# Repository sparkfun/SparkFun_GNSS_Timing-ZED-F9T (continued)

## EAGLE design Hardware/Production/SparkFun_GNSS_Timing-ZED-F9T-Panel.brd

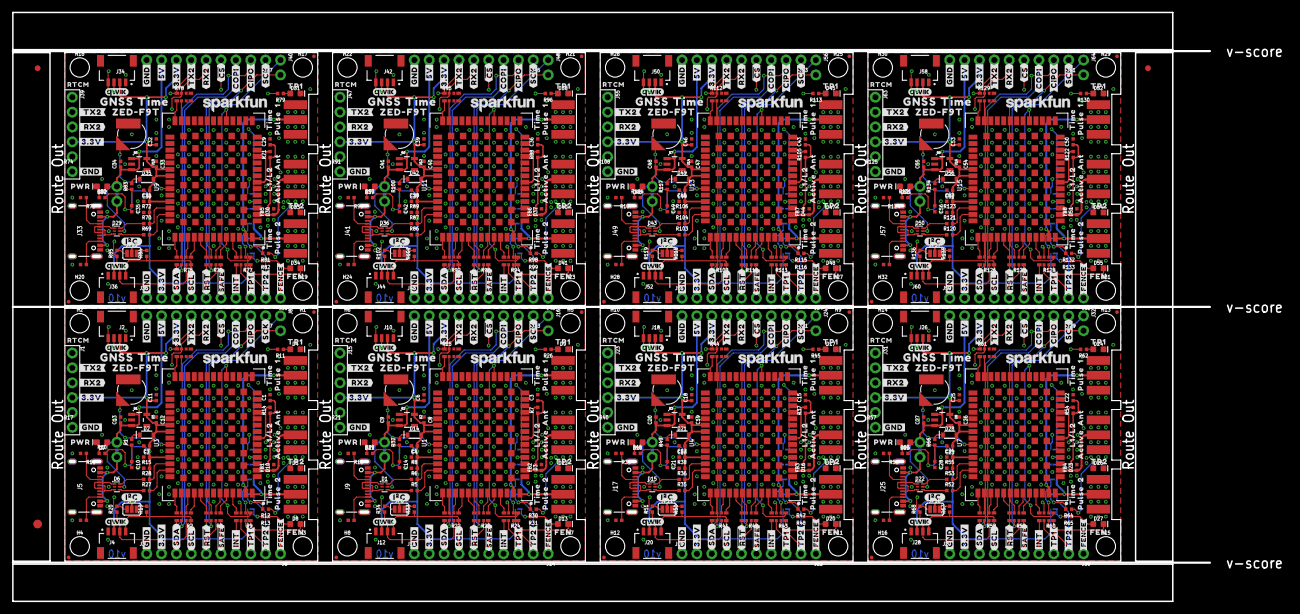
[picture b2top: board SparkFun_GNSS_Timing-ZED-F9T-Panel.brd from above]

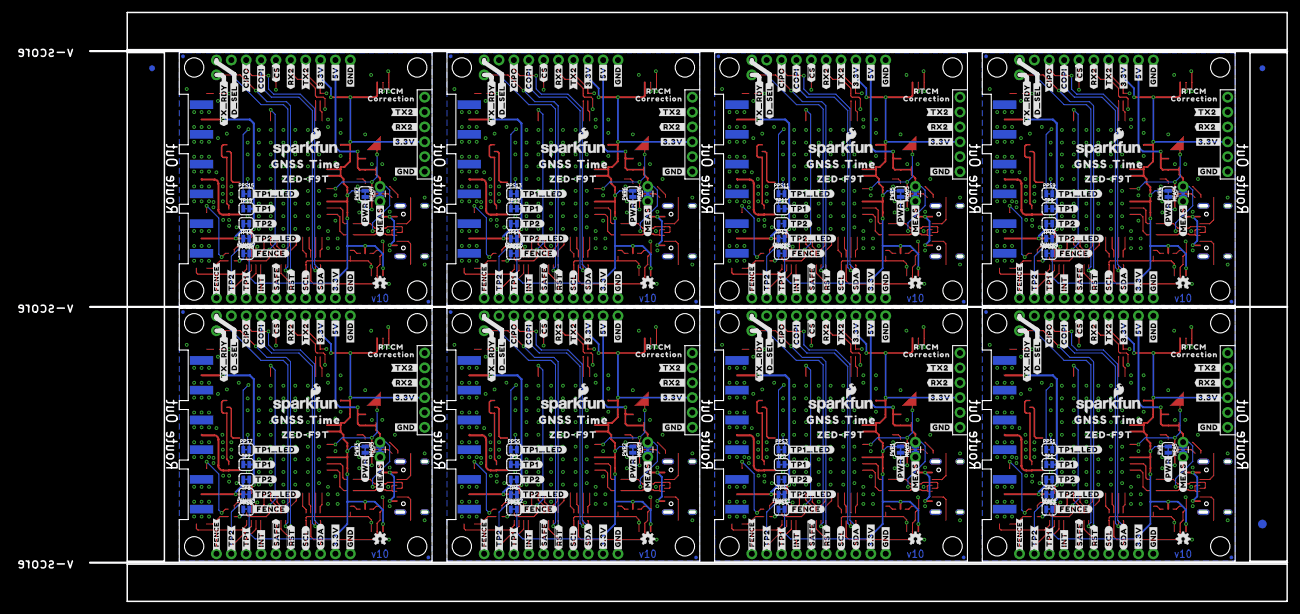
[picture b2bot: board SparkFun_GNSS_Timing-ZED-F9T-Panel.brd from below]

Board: 4 copper layers, 204.5 x 100.6 mm, 1158 parts (379 on the bottom side), 456 nets.

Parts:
B1, B2, B3, B4, B5, B6, B7, B8: 6.8MM_COIN_CELL; ML414H_IV01E
C1, C3, C15, C22, C29, C36, C43, C50: 47pF; 0402-TIGHT
C2, C4, C6, C9, C10, C11, C13, C14, C16, C18, C20, C21, C23, C25, C27, C28, C30, C32, C34, C35, C37, C39, C41, C42, C44, C46, C48, C49, C51, C53, C55, C56: 1.0uF; 0402-TIGHT
C5, C7, C8, C12, C17, C19, C24, C26, C31, C33, C38, C40, C45, C47, C52, C54: 0.1uF; 0402-TIGHT
D1, D6, D15, D22, D29, D36, D43, D50: PRTR5V0U2F; SOT886
D2, D14, D21, D28, D35, D42, D49, D56: 0.5A/40V/420mV; SOD-323
D3, D10, D16, D23, D30, D37, D44, D51: PESD0402-0402T; 0402-TIGHT
D4, D9, D17, D24, D31, D38, D45, D52: YEL; LED-0603
D5, D12, D19, D26, D33, D40, D47, D54: GRN; LED-0603
D7, D11, D18, D25, D32, D39, D46, D53: RED; LED-0603
D8, D13, D20, D27, D34, D41, D48, D55: BLU; LED-0603
E1, E2, E3, E4, E5, E6, E7, E8, E9, E10, E11, E12, E13, E14, E15, E16, E17, E18, E19, E20, E21, E22, E23, E24: SMA; SMA-EDGE
E$1, E$2, E$3, E$4: FIDUCIAL-1X2
E$5, E$6: FIDUCIAL-1.5X3
FB1, FB2, FB3, FB4, FB5, FB6, FB7, FB8: 2.66Ω; 0402-TIGHT
FENCE, FENCE1, FENCE2, FENCE3, FENCE4, FENCE5, FENCE6, FENCE7: JUMPER-SMT_2_NC_TRACE_SILK; SMT-JUMPER_2_NC_TRACE_SILK
H1, H2, H3, H4, H5, H6, H7, H8, H9, H10, H11, H12, H13, H14, H15, H16, H17, H18, H19, H20, H21, H22, H23, H24, H25, H26, H27, H28, H29, H30, H31, H32: STAND-OFF
J1, J15, J23, J31, J39, J47, J55, J63: Radio; 1X06_NO_SILK
J2, J4, J10, J12, J18, J20, J26, J28, J34, J36, J42, J44, J50, J52, J58, J60: Qwiic Right Angle; JST04_1MM_RA
J3, J11, J19, J27, J35, J43, J51, J59: PTH; 1X04_NO_SILK
J5, J9, J17, J25, J33, J41, J49, J57: USB Female Type C Connector; USB-C-16P_4LAYER-PADS
J6, J14, J22, J30, J38, J46, J54, J62: 1X06_NO_SILK
J7, J13, J21, J29, J37, J45, J53, J61: 1X09_NO_SILK
J8, J16, J24, J32, J40, J48, J56, J64: 1X02_NO_SILK
JP1, JP2, JP3, JP4, JP7, JP8, JP9, JP10, JP12, JP13, JP14, JP15, JP17, JP18, JP19, JP20, JP21, JP23, JP24, JP25, JP26, JP28, JP29, JP30, JP31, JP33, JP34, JP35, JP36, JP61, JP71, JP81: FIDUCIALUFIDUCIAL; FIDUCIAL-MICRO
JP5, JP6, JP11, JP16, JP22, JP27, JP32, JP37: JUMPER-SMT_3_NO_SILK; SMT-JUMPER_3_NO_SILK
LOGO1, LOGO6, LOGO11, LOGO16, LOGO21, LOGO26, LOGO31, LOGO36: OSHW-LOGOMINI; OSHW-LOGO-MINI
LOGO2, LOGO7, LOGO12, LOGO17, LOGO22, LOGO27, LOGO32, LOGO37: SFE_LOGO_NAME_FLAME.1_INCH; SFE_LOGO_NAME_FLAME_.1
LOGO3, LOGO4, LOGO8, LOGO10, LOGO13, LOGO15, LOGO18, LOGO20, LOGO23, LOGO25, LOGO28, LOGO30, LOGO33, LOGO35, LOGO38, LOGO40: QWIIC_LOGO_4MM; QWIIC_4MM
LOGO5, LOGO9, LOGO14, LOGO19, LOGO24, LOGO29, LOGO34, LOGO39: SFE_LOGO_NAME.1_INCH; SFE_LOGO_NAME_.1
MEAS, MEAS1, MEAS2, MEAS3, MEAS4, MEAS5, MEAS6, MEAS7: JUMPER-COMBO_2_NC_TRACE; COMBO-JUMPER_2_NC_TRACE
PPS1, PPS2, PPS3, PPS4, PPS5, PPS6, PPS7, PPS8, PPS9, PPS10, PPS11, PPS12, PPS13, PPS14, PPS15, PPS16: JUMPER-SMT_2_NC_TRACE_SILK; SMT-JUMPER_2_NC_TRACE_SILK
PWR, PWR1, PWR2, PWR3, PWR4, PWR5, PWR6, PWR7: JUMPER-SMT_2_NC_TRACE_SILK; SMT-JUMPER_2_NC_TRACE_SILK
R1, R32, R49, R66, R83, R100, R117, R134: 3.3K; 0402-TIGHT
R2, R3, R4, R9, R22, R23, R24, R25, R41, R42, R43, R44, R58, R59, R60, R61, R75, R76, R77, R78, R92, R93, R94, R95, R109, R110, R111, R112, R126, R127, R128, R129: 33; 1206_RA
R5, R6, R27, R28, R35, R36, R52, R53, R69, R70, R86, R87, R103, R104, R120, R121: 27OHM; 0402-TIGHT
R7, R14, R37, R54, R71, R88, R105, R122: 10Ω; 0402-TIGHT
R8, R15, R38, R55, R72, R89, R106, R123: 100k; 0402-TIGHT
R10, R11, R12, R13, R26, R29, R30, R31, R45, R46, R47, R48, R62, R63, R64, R65, R79, R80, R81, R82, R96, R97, R98, R99, R113, R114, R115, R116, R130, R131, R132, R133: 1k; 0402-TIGHT
R16, R17, R18, R21, R39, R40, R56, R57, R73, R74, R90, R91, R107, R108, R124, R125: 5.1k; 0402-TIGHT
R19, R20, R33, R34, R50, R51, R67, R68, R84, R85, R101, R102, R118, R119, R135, R136: 2.2k; 0402-TIGHT
TP1, TP2, TP3, TP4, TP5, TP6, TP7, TP8, TP9, TP10, TP11, TP12, TP13, TP14, TP15, TP16: JUMPER-SMT_2_NC_TRACE_SILK; SMT-JUMPER_2_NC_TRACE_SILK
U1, U3, U4, U7, U9, U11, U13, U15: U-BLOX_ZED_F9T; ZED-F9X
U2, U5, U6, U8, U10, U12, U14, U16: AP2112K-3.3V; SOT23-5
U$1, U$29, U$35, U$36, U$59, U$60, U$88, U$106, U$108, U$109, U$127, U$128, U$165, U$183, U$185, U$186, U$204, U$205, U$242, U$260, U$262, U$263, U$281, U$282, U$319, U$337, U$339, U$340, U$358, U$359, U$396, U$414, U$416, U$417, U$435, U$436, U$473, U$491, U$493, U$494, U$512, U$513, U$550, U$568, U$570, U$571, U$589, U$590: #3#3V#0
U$2, U$6, U$155, U$232, U$309, U$386, U$463, U$540: L1#L20
U$3, U$28, U$89, U$105, U$166, U$182, U$243, U$259, U$320, U$336, U$397, U$413, U$474, U$490, U$551, U$567: #5V#1
U$4, U$27, U$38, U$39, U$61, U$62, U$90, U$104, U$110, U$111, U$129, U$130, U$167, U$181, U$187, U$188, U$206, U$207, U$244, U$258, U$264, U$265, U$283, U$284, U$321, U$335, U$341, U$342, U$360, U$361, U$398, U$412, U$418, U$419, U$437, U$438, U$475, U$489, U$495, U$496, U$514, U$515, U$552, U$566, U$572, U$573, U$591, U$592: #GND#2
U$5, U$8, U$91, U$92, U$168, U$169, U$245, U$246, U$322, U$323, U$399, U$400, U$476, U$477, U$553, U$554: ##CS##4
U$7, U$21, U$80, U$83, U$157, U$160, U$234, U$237, U$311, U$314, U$388, U$391, U$465, U$468, U$542, U$545: TIME0
U$9, U$10, U$93, U$94, U$170, U$171, U$247, U$248, U$324, U$325, U$401, U$402, U$478, U$479, U$555, U$556: #CIPO#6
U$11, U$12, U$95, U$96, U$172, U$173, U$249, U$250, U$326, U$327, U$403, U$404, U$480, U$481, U$557, U$558: #COPI#5
U$13, U$79, U$156, U$233, U$310, U$387, U$464, U$541: ACTIVE1
U$14, U$16, U$97, U$98, U$174, U$175, U$251, U$252, U$328, U$329, U$405, U$406, U$482, U$483, U$559, U$560: #RX2#1
U$15, U$37, U$112, U$113, U$189, U$190, U$266, U$267, U$343, U$344, U$420, U$421, U$497, U$498, U$574, U$575: ##RST##0
U$17, U$53, U$87, U$99, U$164, U$176, U$241, U$253, U$318, U$330, U$395, U$407, U$472, U$484, U$549, U$561: #SCL#3
U$18, U$22, U$100, U$101, U$177, U$178, U$254, U$255, U$331, U$332, U$408, U$409, U$485, U$486, U$562, U$563: #SDA#2
U$19, U$25, U$81, U$84, U$158, U$161, U$235, U$238, U$312, U$315, U$389, U$392, U$466, U$469, U$543, U$546: PULSE1
U$20, U$82, U$159, U$236, U$313, U$390, U$467, U$544: 12
U$23, U$24, U$102, U$103, U$179, U$180, U$256, U$257, U$333, U$334, U$410, U$411, U$487, U$488, U$564, U$565: #TX2#0
U$26, U$85, U$162, U$239, U$316, U$393, U$470, U$547: 20
U$30, U$107, U$184, U$261, U$338, U$415, U$492, U$569: #SCK#5
U$31, U$86, U$163, U$240, U$317, U$394, U$471, U$548: ANT1
U$32, U$136, U$213, U$290, U$367, U$444, U$521, U$598: #_TX2#0
U$33, U$135, U$212, U$289, U$366, U$443, U$520, U$597: #D_SEL#1
U$34, U$77, U$146, U$153, U$223, U$230, U$300, U$307, U$377, U$384, U$454, U$461, U$531, U$538, U$608, U$615: ZED#F9T0
U$40, U$70, U$144, U$151, U$221, U$228, U$298, U$305, U$375, U$382, U$452, U$459, U$529, U$536, U$606, U$613: GNSS0
U$41, U$114, U$191, U$268, U$345, U$422, U$499, U$576: ##SAFE##1
U$42, U$43, U$115, U$116, U$192, U$193, U$269, U$270, U$346, U$347, U$423, U$424, U$500, U$501, U$577, U$578: #INT#2
U$44, U$65, U$121, U$133, U$198, U$210, U$275, U$287, U$352, U$364, U$429, U$441, U$506, U$518, U$583, U$595: #FENCE#0
U$45, U$126, U$203, U$280, U$357, U$434, U$511, U$588: #TP2_LED#0
U$46, U$47, U$117, U$118, U$194, U$195, U$271, U$272, U$348, U$349, U$425, U$426, U$502, U$503, U$579, U$580: #TP1#3
U$48, U$49, U$119, U$120, U$196, U$197, U$273, U$274, U$350, U$351, U$427, U$428, U$504, U$505, U$581, U$582: #TP2#4
U$50, U$123, U$200, U$277, U$354, U$431, U$508, U$585: #TP2#0
U$51, U$122, U$199, U$276, U$353, U$430, U$507, U$584: #_FENCE#0
U$52, U$124, U$201, U$278, U$355, U$432, U$509, U$586: #TP1#0
U$54, U$125, U$202, U$279, U$356, U$433, U$510, U$587: #TP1_LED#0
U$55, U$139, U$216, U$293, U$370, U$447, U$524, U$601: #_RX2#0
U$56, U$137, U$214, U$291, U$368, U$445, U$522, U$599: PWR0
U$57, U$138, U$215, U$292, U$369, U$446, U$523, U$600: #PWR#0
U$58, U$140, U$217, U$294, U$371, U$448, U$525, U$602: #RX2_#0
U$63, U$131, U$208, U$285, U$362, U$439, U$516, U$593: TP10
U$64, U$132, U$209, U$286, U$363, U$440, U$517, U$594: TP21
U$66, U$141, U$218, U$295, U$372, U$449, U$526, U$603: #TX2_#0
U$67, U$134, U$211, U$288, U$365, U$442, U$519, U$596: #TX_RDY#0
U$68, U$142, U$219, U$296, U$373, U$450, U$527, U$604: #MEAS#0
U$69, U$143, U$220, U$297, U$374, U$451, U$528, U$605: #I�C#0
U$71, U$74, U$145, U$152, U$222, U$229, U$299, U$306, U$376, U$383, U$453, U$460, U$530, U$537, U$607, U$614: TIME1
U$72, U$147, U$224, U$301, U$378, U$455, U$532, U$609: ##SAFE##0
U$73, U$148, U$225, U$302, U$379, U$456, U$533, U$610: RTCM0
U$75, U$149, U$226, U$303, U$380, U$457, U$534, U$611: CORRECTION1
U$76, U$150, U$227, U$304, U$381, U$458, U$535, U$612: RTCM_0
U$78, U$154, U$231, U$308, U$385, U$462, U$539, U$616: FEN0

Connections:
3.3V: C2.1, C7.2, C11.1, C12.2, D2.A, FENCE.2, J1.4, J2.2, J3.2, J4.2, J7.7, JP5.2, PWR.2, R15.2, U3.33, U3.34, U3.38, U5.5
3.3V1: C4.1, C5.2, C6.1, C8.2, D14.A, FENCE1.2, J10.2, J11.2, J12.2, J13.7, J15.4, JP6.2, PWR1.2, R8.2, U1.33, U1.34, U1.38, U2.5
3.3V2: C16.1, C17.2, C18.1, C19.2, D21.A, FENCE2.2, J18.2, J19.2, J20.2, J21.7, J23.4, JP11.2, PWR2.2, R38.2, U4.33, U4.34, U4.38, U6.5
3.3V3: C23.1, C24.2, C25.1, C26.2, D28.A, FENCE3.2, J26.2, J27.2, J28.2, J29.7, J31.4, JP16.2, PWR3.2, R55.2, U7.33, U7.34, U7.38, U8.5
3.3V4: C30.1, C31.2, C32.1, C33.2, D35.A, FENCE4.2, J34.2, J35.2, J36.2, J37.7, J39.4, JP22.2, PWR4.2, R72.2, U9.33, U9.34, U9.38, U10.5
3.3V5: C37.1, C38.2, C39.1, C40.2, D42.A, FENCE5.2, J42.2, J43.2, J44.2, J45.7, J47.4, JP27.2, PWR5.2, R89.2, U11.33, U11.34, U11.38, U12.5
3.3V6: C44.1, C45.2, C46.1, C47.2, D49.A, FENCE6.2, J50.2, J51.2, J52.2, J53.7, J55.4, JP32.2, PWR6.2, R106.2, U13.33, U13.34, U13.38, U14.5
3.3V7: C51.1, C52.2, C53.1, C54.2, D56.A, FENCE7.2, J58.2, J59.2, J60.2, J61.7, J63.4, JP37.2, PWR7.2, R123.2, U15.33, U15.34, U15.38, U16.5
5V: C13.1, D6.5, J7.8, MEAS.2, MEAS.4, U5.1, U5.3
5V1: C9.1, D1.5, J13.8, MEAS1.2, MEAS1.4, U2.1, U2.3
5V2: C20.1, D15.5, J21.8, MEAS2.2, MEAS2.4, U6.1, U6.3
5V3: C27.1, D22.5, J29.8, MEAS3.2, MEAS3.4, U8.1, U8.3
5V4: C34.1, D29.5, J37.8, MEAS4.2, MEAS4.4, U10.1, U10.3
5V5: C41.1, D36.5, J45.8, MEAS5.2, MEAS5.4, U12.1, U12.3
5V6: C48.1, D43.5, J53.8, MEAS6.2, MEAS6.4, U14.1, U14.3
5V7: C55.1, D50.5, J61.8, MEAS7.2, MEAS7.4, U16.1, U16.3
!RESET!: J6.6, R3.P7
!RESET!1: J14.6, R23.P7
!RESET!2: J22.6, R42.P7
!RESET!3: J30.6, R59.P7
!RESET!4: J38.6, R76.P7
!RESET!5: J46.6, R93.P7
!RESET!6: J54.6, R110.P7
!RESET!7: J62.6, R127.P7
!RESET!_LV: R3.P2, U3.49
!RESET!_LV1: R23.P2, U1.49
!RESET!_LV2: R42.P2, U4.49
!RESET!_LV3: R59.P2, U7.49
!RESET!_LV4: R76.P2, U9.49
!RESET!_LV5: R93.P2, U11.49
!RESET!_LV6: R110.P2, U13.49
!RESET!_LV7: R127.P2, U15.49
!SAFE!: J6.5, R3.P8
!SAFE!1: J14.5, R23.P8
!SAFE!2: J22.5, R42.P8
!SAFE!3: J30.5, R59.P8
!SAFE!4: J38.5, R76.P8
!SAFE!5: J46.5, R93.P8
!SAFE!6: J54.5, R110.P8
!SAFE!7: J62.5, R127.P8
!SAFE!_LV: R3.P1, U3.50
!SAFE!_LV1: R23.P1, U1.50
!SAFE!_LV2: R42.P1, U4.50
!SAFE!_LV3: R59.P1, U7.50
!SAFE!_LV4: R76.P1, U9.50
!SAFE!_LV5: R93.P1, U11.50
!SAFE!_LV6: R110.P1, U13.50
!SAFE!_LV7: R127.P1, U15.50
ANT_VCC: C1.1, FB1.2, R14.1
ANT_VCC1: C3.1, FB2.2, R7.1
ANT_VCC2: C15.1, FB3.2, R37.1
ANT_VCC3: C22.1, FB4.2, R54.1
ANT_VCC4: C29.1, FB5.2, R71.1
ANT_VCC5: C36.1, FB6.2, R88.1
ANT_VCC6: C43.1, FB7.2, R105.1
ANT_VCC7: C50.1, FB8.2, R122.1
CC1: J5.A5, R17.2
CC2: J5.B5, R16.2
CC3: J9.A5, R21.2
CC4: J9.B5, R18.2
CC5: J17.A5, R40.2
CC6: J17.B5, R39.2
CC7: J25.A5, R57.2
CC8: J25.B5, R56.2
CC9: J33.A5, R74.2
CC10: J33.B5, R73.2
CC11: J41.A5, R91.2
CC12: J41.B5, R90.2
CC13: J49.A5, R108.2
CC14: J49.B5, R107.2
CC15: J57.A5, R125.2
CC16: J57.B5, R124.2
D+: D6.4, R27.1
D+1: D1.4, R5.1
D+2: D15.4, R35.1
D+3: D22.4, R52.1
D+4: D29.4, R69.1
D+5: D36.4, R86.1
D+6: D43.4, R103.1
D+7: D50.4, R120.1
D-: D6.6, R28.1
D-1: D1.6, R6.1
D-2: D15.6, R36.1
D-3: D22.6, R53.1
D-4: D29.6, R70.1
D-5: D36.6, R87.1
D-6: D43.6, R104.1
D-7: D50.6, R121.1
DSEL_LV: R3.P3, U3.47
DSEL_LV1: R23.P3, U1.47
DSEL_LV2: R42.P3, U4.47
DSEL_LV3: R59.P3, U7.47
DSEL_LV4: R76.P3, U9.47
DSEL_LV5: R93.P3, U11.47
DSEL_LV6: R110.P3, U13.47
DSEL_LV7: R127.P3, U15.47
D_SEL: J8.1, R3.P6
D_SEL1: J16.1, R23.P6
D_SEL2: J24.1, R42.P6
D_SEL3: J32.1, R59.P6
D_SEL4: J40.1, R76.P6
D_SEL5: J48.1, R93.P6
D_SEL6: J56.1, R110.P6
D_SEL7: J64.1, R127.P6
EXTINT: J6.4, R9.P5
EXTINT1: J14.4, R24.P5
EXTINT2: J22.4, R43.P5
EXTINT3: J30.4, R60.P5
EXTINT4: J38.4, R77.P5
EXTINT5: J46.4, R94.P5
EXTINT6: J54.4, R111.P5
EXTINT7: J62.4, R128.P5
EXTINT_LV: R9.P4, U3.51
EXTINT_LV1: R24.P4, U1.51
EXTINT_LV2: R43.P4, U4.51
EXTINT_LV3: R60.P4, U7.51
EXTINT_LV4: R77.P4, U9.51
EXTINT_LV5: R94.P4, U11.51
EXTINT_LV6: R111.P4, U13.51
EXTINT_LV7: R128.P4, U15.51
FENCE_LV: R9.P1, U3.19
FENCE_LV1: R24.P1, U1.19
FENCE_LV2: R43.P1, U4.19
FENCE_LV3: R60.P1, U7.19
FENCE_LV4: R77.P1, U9.19
FENCE_LV5: R94.P1, U11.19
FENCE_LV6: R111.P1, U13.19
FENCE_LV7: R128.P1, U15.19
FENCE_STAT: D8.C, J6.1, R9.P8
FENCE_STAT1: D13.C, J14.1, R24.P8
FENCE_STAT2: D20.C, J22.1, R43.P8
FENCE_STAT3: D27.C, J30.1, R60.P8
FENCE_STAT4: D34.C, J38.1, R77.P8
FENCE_STAT5: D41.C, J46.1, R94.P8
FENCE_STAT6: D48.C, J54.1, R111.P8
FENCE_STAT7: D55.C, J62.1, R128.P8
GND: B1.-, C1.2, C2.2, C7.1, C10.2, C11.2, C12.1, C13.2, D4.C, D5.C, D6.2, D7.C, D10.2, E1.GND@0, E1.GND@1, E1.GND@2, E1.GND@3, E2.GND@0, E2.GND@1, E2.GND@2, E2.GND@3, E3.GND@0, E3.GND@1, E3.GND@2, E3.GND@3, J1.6, J2.1, J3.1, J4.1, J5.GND, J5.GND2, J7.9, R15.1, R16.1, R17.1, U3.1, U3.3, U3.12, U3.14, U3.32, U3.37, U3.41, U3.48, U3.G1, U3.G2, U3.G3, U3.G4, U3.G5, U3.G6, U3.G7, U3.G8, U3.G9, U3.G10, U3.G11, U3.G12, U3.G13, U3.G14, U3.G15, U3.G16, U3.G17, U3.G18, U3.G19, U3.G20, U3.G21, U3.G22, U3.G23, U3.G24, U3.G25, U3.G26, U3.G27, U3.G28, U3.G29, U3.G30, U3.G31, U3.G32, U3.G33, U3.G34, U3.G35, U3.G36, U3.G37, U3.G38, U3.G39, U3.G40, U3.G41, U3.G42, U3.G43, U3.G44, U3.G45, U3.G46, U3.G47, U3.G48, U5.2
GND1: B2.-, C3.2, C4.2, C5.1, C6.2, C8.1, C9.2, C14.2, D1.2, D3.2, D9.C, D11.C, D12.C, E4.GND@0, E4.GND@1, E4.GND@2, E4.GND@3, E5.GND@0, E5.GND@1, E5.GND@2, E5.GND@3, E6.GND@0, E6.GND@1, E6.GND@2, E6.GND@3, J9.GND, J9.GND2, J10.1, J11.1, J12.1, J13.9, J15.6, R8.1, R18.1, R21.1, U1.1, U1.3, U1.12, U1.14, U1.32, U1.37, U1.41, U1.48, U1.G1, U1.G2, U1.G3, U1.G4, U1.G5, U1.G6, U1.G7, U1.G8, U1.G9, U1.G10, U1.G11, U1.G12, U1.G13, U1.G14, U1.G15, U1.G16, U1.G17, U1.G18, U1.G19, U1.G20, U1.G21, U1.G22, U1.G23, U1.G24, U1.G25, U1.G26, U1.G27, U1.G28, U1.G29, U1.G30, U1.G31, U1.G32, U1.G33, U1.G34, U1.G35, U1.G36, U1.G37, U1.G38, U1.G39, U1.G40, U1.G41, U1.G42, U1.G43, U1.G44, U1.G45, U1.G46, U1.G47, U1.G48, U2.2
GND2: B3.-, C15.2, C16.2, C17.1, C18.2, C19.1, C20.2, C21.2, D15.2, D16.2, D17.C, D18.C, D19.C, E7.GND@0, E7.GND@1, E7.GND@2, E7.GND@3, E8.GND@0, E8.GND@1, E8.GND@2, E8.GND@3, E9.GND@0, E9.GND@1, E9.GND@2, E9.GND@3, J17.GND, J17.GND2, J18.1, J19.1, J20.1, J21.9, J23.6, R38.1, R39.1, R40.1, U4.1, U4.3, U4.12, U4.14, U4.32, U4.37, U4.41, U4.48, U4.G1, U4.G2, U4.G3, U4.G4, U4.G5, U4.G6, U4.G7, U4.G8, U4.G9, U4.G10, U4.G11, U4.G12, U4.G13, U4.G14, U4.G15, U4.G16, U4.G17, U4.G18, U4.G19, U4.G20, U4.G21, U4.G22, U4.G23, U4.G24, U4.G25, U4.G26, U4.G27, U4.G28, U4.G29, U4.G30, U4.G31, U4.G32, U4.G33, U4.G34, U4.G35, U4.G36, U4.G37, U4.G38, U4.G39, U4.G40, U4.G41, U4.G42, U4.G43, U4.G44, U4.G45, U4.G46, U4.G47, U4.G48, U6.2
GND3: B4.-, C22.2, C23.2, C24.1, C25.2, C26.1, C27.2, C28.2, D22.2, D23.2, D24.C, D25.C, D26.C, E10.GND@0, E10.GND@1, E10.GND@2, E10.GND@3, E11.GND@0, E11.GND@1, E11.GND@2, E11.GND@3, E12.GND@0, E12.GND@1, E12.GND@2, E12.GND@3, J25.GND, J25.GND2, J26.1, J27.1, J28.1, J29.9, J31.6, R55.1, R56.1, R57.1, U7.1, U7.3, U7.12, U7.14, U7.32, U7.37, U7.41, U7.48, U7.G1, U7.G2, U7.G3, U7.G4, U7.G5, U7.G6, U7.G7, U7.G8, U7.G9, U7.G10, U7.G11, U7.G12, U7.G13, U7.G14, U7.G15, U7.G16, U7.G17, U7.G18, U7.G19, U7.G20, U7.G21, U7.G22, U7.G23, U7.G24, U7.G25, U7.G26, U7.G27, U7.G28, U7.G29, U7.G30, U7.G31, U7.G32, U7.G33, U7.G34, U7.G35, U7.G36, U7.G37, U7.G38, U7.G39, U7.G40, U7.G41, U7.G42, U7.G43, U7.G44, U7.G45, U7.G46, U7.G47, U7.G48, U8.2
GND4: B5.-, C29.2, C30.2, C31.1, C32.2, C33.1, C34.2, C35.2, D29.2, D30.2, D31.C, D32.C, D33.C, E13.GND@0, E13.GND@1, E13.GND@2, E13.GND@3, E14.GND@0, E14.GND@1, E14.GND@2, E14.GND@3, E15.GND@0, E15.GND@1, E15.GND@2, E15.GND@3, J33.GND, J33.GND2, J34.1, J35.1, J36.1, J37.9, J39.6, R72.1, R73.1, R74.1, U9.1, U9.3, U9.12, U9.14, U9.32, U9.37, U9.41, U9.48, U9.G1, U9.G2, U9.G3, U9.G4, U9.G5, U9.G6, U9.G7, U9.G8, U9.G9, U9.G10, U9.G11, U9.G12, U9.G13, U9.G14, U9.G15, U9.G16, U9.G17, U9.G18, U9.G19, U9.G20, U9.G21, U9.G22, U9.G23, U9.G24, U9.G25, U9.G26, U9.G27, U9.G28, U9.G29, U9.G30, U9.G31, U9.G32, U9.G33, U9.G34, U9.G35, U9.G36, U9.G37, U9.G38, U9.G39, U9.G40, U9.G41, U9.G42, U9.G43, U9.G44, U9.G45, U9.G46, U9.G47, U9.G48, U10.2
GND5: B6.-, C36.2, C37.2, C38.1, C39.2, C40.1, C41.2, C42.2, D36.2, D37.2, D38.C, D39.C, D40.C, E16.GND@0, E16.GND@1, E16.GND@2, E16.GND@3, E17.GND@0, E17.GND@1, E17.GND@2, E17.GND@3, E18.GND@0, E18.GND@1, E18.GND@2, E18.GND@3, J41.GND, J41.GND2, J42.1, J43.1, J44.1, J45.9, J47.6, R89.1, R90.1, R91.1, U11.1, U11.3, U11.12, U11.14, U11.32, U11.37, U11.41, U11.48, U11.G1, U11.G2, U11.G3, U11.G4, U11.G5, U11.G6, U11.G7, U11.G8, U11.G9, U11.G10, U11.G11, U11.G12, U11.G13, U11.G14, U11.G15, U11.G16, U11.G17, U11.G18, U11.G19, U11.G20, U11.G21, U11.G22, U11.G23, U11.G24, U11.G25, U11.G26, U11.G27, U11.G28, U11.G29, U11.G30, U11.G31, U11.G32, U11.G33, U11.G34, U11.G35, U11.G36, U11.G37, U11.G38, U11.G39, U11.G40, U11.G41, U11.G42, U11.G43, U11.G44, U11.G45, U11.G46, U11.G47, U11.G48, U12.2
GND6: B7.-, C43.2, C44.2, C45.1, C46.2, C47.1, C48.2, C49.2, D43.2, D44.2, D45.C, D46.C, D47.C, E19.GND@0, E19.GND@1, E19.GND@2, E19.GND@3, E20.GND@0, E20.GND@1, E20.GND@2, E20.GND@3, E21.GND@0, E21.GND@1, E21.GND@2, E21.GND@3, J49.GND, J49.GND2, J50.1, J51.1, J52.1, J53.9, J55.6, R106.1, R107.1, R108.1, U13.1, U13.3, U13.12, U13.14, U13.32, U13.37, U13.41, U13.48, U13.G1, U13.G2, U13.G3, U13.G4, U13.G5, U13.G6, U13.G7, U13.G8, U13.G9, U13.G10, U13.G11, U13.G12, U13.G13, U13.G14, U13.G15, U13.G16, U13.G17, U13.G18, U13.G19, U13.G20, U13.G21, U13.G22, U13.G23, U13.G24, U13.G25, U13.G26, U13.G27, U13.G28, U13.G29, U13.G30, U13.G31, U13.G32, U13.G33, U13.G34, U13.G35, U13.G36, U13.G37, U13.G38, U13.G39, U13.G40, U13.G41, U13.G42, U13.G43, U13.G44, U13.G45, U13.G46, U13.G47, U13.G48, U14.2
GND7: B8.-, C50.2, C51.2, C52.1, C53.2, C54.1, C55.2, C56.2, D50.2, D51.2, D52.C, D53.C, D54.C, E22.GND@0, E22.GND@1, E22.GND@2, E22.GND@3, E23.GND@0, E23.GND@1, E23.GND@2, E23.GND@3, E24.GND@0, E24.GND@1, E24.GND@2, E24.GND@3, J57.GND, J57.GND2, J58.1, J59.1, J60.1, J61.9, J63.6, R123.1, R124.1, R125.1, U15.1, U15.3, U15.12, U15.14, U15.32, U15.37, U15.41, U15.48, U15.G1, U15.G2, U15.G3, U15.G4, U15.G5, U15.G6, U15.G7, U15.G8, U15.G9, U15.G10, U15.G11, U15.G12, U15.G13, U15.G14, U15.G15, U15.G16, U15.G17, U15.G18, U15.G19, U15.G20, U15.G21, U15.G22, U15.G23, U15.G24, U15.G25, U15.G26, U15.G27, U15.G28, U15.G29, U15.G30, U15.G31, U15.G32, U15.G33, U15.G34, U15.G35, U15.G36, U15.G37, U15.G38, U15.G39, U15.G40, U15.G41, U15.G42, U15.G43, U15.G44, U15.G45, U15.G46, U15.G47, U15.G48, U16.2
GPS_ANT1: D10.1, E1.SIG, FB1.1, U3.2
GPS_ANT2: D3.1, E4.SIG, FB2.1, U1.2
GPS_ANT3: D16.1, E7.SIG, FB3.1, U4.2
GPS_ANT4: D23.1, E10.SIG, FB4.1, U7.2
GPS_ANT5: D30.1, E13.SIG, FB5.1, U9.2
GPS_ANT6: D37.1, E16.SIG, FB6.1, U11.2
GPS_ANT7: D44.1, E19.SIG, FB7.1, U13.2
GPS_ANT8: D51.1, E22.SIG, FB8.1, U15.2
unnamed: R5.2, U1.40
unnamed: D4.A, R11.1
unnamed: PPS1.1, R11.2
unnamed: J5.VBUS1, J5.VBUS2, MEAS.1, MEAS.3
unnamed: R9.P3, TP1.1
unnamed: D2.C, R1.2
unnamed: R9.P2, TP2.1
unnamed: R6.2, U1.39
unnamed: R7.2, U1.7
unnamed: J9.VBUS1, J9.VBUS2, MEAS1.1, MEAS1.3
unnamed: R27.2, U3.40
unnamed: R28.2, U3.39
unnamed: R14.2, U3.7
unnamed: D7.A, R10.1
unnamed: D9.A, R26.1
unnamed: D5.A, R12.1
unnamed: PPS2.1, R12.2
unnamed: D8.A, R13.1
unnamed: FENCE.1, R13.2
unnamed: PWR.1, R10.2
unnamed: JP5.1, R20.2
unnamed: JP5.3, R19.2
unnamed: PPS3.1, R26.2
unnamed: D11.A, R29.1
unnamed: D12.A, R30.1
unnamed: PPS4.1, R30.2
unnamed: D13.A, R31.1
unnamed: FENCE1.1, R31.2
unnamed: PWR1.1, R29.2
unnamed: D14.C, R32.2
unnamed: JP6.1, R34.2
unnamed: JP6.3, R33.2
unnamed: R24.P3, TP3.1
unnamed: R24.P2, TP4.1
unnamed: R35.2, U4.40
unnamed: R36.2, U4.39
unnamed: R37.2, U4.7
unnamed: J17.VBUS1, J17.VBUS2, MEAS2.1, MEAS2.3
unnamed: D17.A, R45.1
unnamed: PPS5.1, R45.2
unnamed: D18.A, R46.1
unnamed: D19.A, R47.1
unnamed: PPS6.1, R47.2
unnamed: D20.A, R48.1
unnamed: FENCE2.1, R48.2
unnamed: PWR2.1, R46.2
unnamed: D21.C, R49.2
unnamed: JP11.1, R51.2
unnamed: JP11.3, R50.2
unnamed: R43.P3, TP5.1
unnamed: R43.P2, TP6.1
unnamed: R52.2, U7.40
unnamed: R53.2, U7.39
unnamed: R54.2, U7.7
unnamed: J25.VBUS1, J25.VBUS2, MEAS3.1, MEAS3.3
unnamed: D24.A, R62.1
unnamed: PPS7.1, R62.2
unnamed: D25.A, R63.1
unnamed: D26.A, R64.1
unnamed: PPS8.1, R64.2
unnamed: D27.A, R65.1
unnamed: FENCE3.1, R65.2
unnamed: PWR3.1, R63.2
unnamed: D28.C, R66.2
unnamed: JP16.1, R68.2
unnamed: JP16.3, R67.2
unnamed: R60.P3, TP7.1
unnamed: R60.P2, TP8.1
unnamed: R69.2, U9.40
unnamed: R70.2, U9.39
unnamed: R71.2, U9.7
unnamed: J33.VBUS1, J33.VBUS2, MEAS4.1, MEAS4.3
unnamed: D31.A, R79.1
unnamed: PPS9.1, R79.2
unnamed: D32.A, R80.1
unnamed: D33.A, R81.1
unnamed: PPS10.1, R81.2
unnamed: D34.A, R82.1
unnamed: FENCE4.1, R82.2
unnamed: PWR4.1, R80.2
unnamed: D35.C, R83.2
unnamed: JP22.1, R85.2
unnamed: JP22.3, R84.2
unnamed: R77.P3, TP9.1
unnamed: R77.P2, TP10.1
unnamed: R86.2, U11.40
unnamed: R87.2, U11.39
unnamed: R88.2, U11.7
unnamed: J41.VBUS1, J41.VBUS2, MEAS5.1, MEAS5.3
unnamed: D38.A, R96.1
unnamed: PPS11.1, R96.2
unnamed: D39.A, R97.1
unnamed: D40.A, R98.1
unnamed: PPS12.1, R98.2
unnamed: D41.A, R99.1
unnamed: FENCE5.1, R99.2
unnamed: PWR5.1, R97.2
unnamed: D42.C, R100.2
unnamed: JP27.1, R102.2
unnamed: JP27.3, R101.2
unnamed: R94.P3, TP11.1
unnamed: R94.P2, TP12.1
unnamed: R103.2, U13.40
unnamed: R104.2, U13.39
unnamed: R105.2, U13.7
unnamed: J49.VBUS1, J49.VBUS2, MEAS6.1, MEAS6.3
unnamed: D45.A, R113.1
unnamed: PPS13.1, R113.2
unnamed: D46.A, R114.1
unnamed: D47.A, R115.1
unnamed: PPS14.1, R115.2
unnamed: D48.A, R116.1
unnamed: FENCE6.1, R116.2
unnamed: PWR6.1, R114.2
unnamed: D49.C, R117.2
unnamed: JP32.1, R119.2
unnamed: JP32.3, R118.2
unnamed: R111.P3, TP13.1
unnamed: R111.P2, TP14.1
unnamed: R120.2, U15.40
unnamed: R121.2, U15.39
unnamed: R122.2, U15.7
unnamed: J57.VBUS1, J57.VBUS2, MEAS7.1, MEAS7.3
unnamed: D52.A, R130.1
unnamed: PPS15.1, R130.2
unnamed: D53.A, R131.1
unnamed: D54.A, R132.1
unnamed: PPS16.1, R132.2
unnamed: D55.A, R133.1
unnamed: FENCE7.1, R133.2
unnamed: PWR7.1, R131.2
unnamed: D56.C, R134.2
unnamed: JP37.1, R136.2
unnamed: JP37.3, R135.2
unnamed: R128.P3, TP15.1
unnamed: R128.P2, TP16.1
PPS1_STAT: J6.3, PPS1.2, R9.P6
PPS1_STAT1: J14.3, PPS3.2, R24.P6
PPS1_STAT2: J22.3, PPS5.2, R43.P6
PPS1_STAT3: J30.3, PPS7.2, R60.P6
PPS1_STAT4: J38.3, PPS9.2, R77.P6
PPS1_STAT5: J46.3, PPS11.2, R94.P6
PPS1_STAT6: J54.3, PPS13.2, R111.P6
PPS1_STAT7: J62.3, PPS15.2, R128.P6
PPS2_STAT: J6.2, PPS2.2, R9.P7
PPS2_STAT1: J14.2, PPS4.2, R24.P7
PPS2_STAT2: J22.2, PPS6.2, R43.P7
PPS2_STAT3: J30.2, PPS8.2, R60.P7
PPS2_STAT4: J38.2, PPS10.2, R77.P7
PPS2_STAT5: J46.2, PPS12.2, R94.P7
PPS2_STAT6: J54.2, PPS14.2, R111.P7
PPS2_STAT7: J62.2, PPS16.2, R128.P7
RX1_LV: R2.P3, U3.43
RX1_LV1: R22.P3, U1.43
RX1_LV2: R41.P3, U4.43
RX1_LV3: R58.P3, U7.43
RX1_LV4: R75.P3, U9.43
RX1_LV5: R92.P3, U11.43
RX1_LV6: R109.P3, U13.43
RX1_LV7: R126.P3, U15.43
RX2_LV: R4.P2, U3.26
RX2_LV1: R25.P2, U1.26
RX2_LV2: R44.P2, U4.26
RX2_LV3: R61.P2, U7.26
RX2_LV4: R78.P2, U9.26
RX2_LV5: R95.P2, U11.26
RX2_LV6: R112.P2, U13.26
RX2_LV7: R129.P2, U15.26
RXI1: J13.5, J15.3, R25.P7
RXI2: J1.3, J7.5, R4.P7
RXI3: J21.5, J23.3, R44.P7
RXI4: J29.5, J31.3, R61.P7
RXI5: J37.5, J39.3, R78.P7
RXI6: J45.5, J47.3, R95.P7
RXI7: J53.5, J55.3, R112.P7
RXI8: J61.5, J63.3, R129.P7
RXI/COPI: J7.3, R2.P6
RXI/COPI1: J13.3, R22.P6
RXI/COPI2: J21.3, R41.P6
RXI/COPI3: J29.3, R58.P6
RXI/COPI4: J37.3, R75.P6
RXI/COPI5: J45.3, R92.P6
RXI/COPI6: J53.3, R109.P6
RXI/COPI7: J61.3, R126.P6
SCL/SCK: J2.4, J3.4, J4.4, J7.1, R2.P8, R19.1
SCL/SCK1: J10.4, J11.4, J12.4, J13.1, R22.P8, R33.1
SCL/SCK2: J18.4, J19.4, J20.4, J21.1, R41.P8, R50.1
SCL/SCK3: J26.4, J27.4, J28.4, J29.1, R58.P8, R67.1
SCL/SCK4: J34.4, J35.4, J36.4, J37.1, R75.P8, R84.1
SCL/SCK5: J42.4, J43.4, J44.4, J45.1, R92.P8, R101.1
SCL/SCK6: J50.4, J51.4, J52.4, J53.1, R109.P8, R118.1
SCL/SCK7: J58.4, J59.4, J60.4, J61.1, R126.P8, R135.1
SCL_LV: R2.P1, U3.45
SCL_LV1: R22.P1, U1.45
SCL_LV2: R41.P1, U4.45
SCL_LV3: R58.P1, U7.45
SCL_LV4: R75.P1, U9.45
SCL_LV5: R92.P1, U11.45
SCL_LV6: R109.P1, U13.45
SCL_LV7: R126.P1, U15.45
SDA/!CS: J2.3, J3.3, J4.3, J7.4, R2.P7, R20.1
SDA/!CS1: J10.3, J11.3, J12.3, J13.4, R22.P7, R34.1
SDA/!CS2: J18.3, J19.3, J20.3, J21.4, R41.P7, R51.1
SDA/!CS3: J26.3, J27.3, J28.3, J29.4, R58.P7, R68.1
SDA/!CS4: J34.3, J35.3, J36.3, J37.4, R75.P7, R85.1
SDA/!CS5: J42.3, J43.3, J44.3, J45.4, R92.P7, R102.1
SDA/!CS6: J50.3, J51.3, J52.3, J53.4, R109.P7, R119.1
SDA/!CS7: J58.3, J59.3, J60.3, J61.4, R126.P7, R136.1
SDA_LV: R2.P2, U3.44
SDA_LV1: R22.P2, U1.44
SDA_LV2: R41.P2, U4.44
SDA_LV3: R58.P2, U7.44
SDA_LV4: R75.P2, U9.44
SDA_LV5: R92.P2, U11.44
SDA_LV6: R109.P2, U13.44
SDA_LV7: R126.P2, U15.44
TP1_LV: E2.SIG, TP1.2, U3.53
TP1_LV1: E5.SIG, TP3.2, U1.53
TP1_LV2: E8.SIG, TP5.2, U4.53
TP1_LV3: E11.SIG, TP7.2, U7.53
TP1_LV4: E14.SIG, TP9.2, U9.53
TP1_LV5: E17.SIG, TP11.2, U11.53
TP1_LV6: E20.SIG, TP13.2, U13.53
TP1_LV7: E23.SIG, TP15.2, U15.53
TP2_LV: E3.SIG, TP2.2, U3.54
TP2_LV1: E6.SIG, TP4.2, U1.54
TP2_LV2: E9.SIG, TP6.2, U4.54
TP2_LV3: E12.SIG, TP8.2, U7.54
TP2_LV4: E15.SIG, TP10.2, U9.54
TP2_LV5: E18.SIG, TP12.2, U11.54
TP2_LV6: E21.SIG, TP14.2, U13.54
TP2_LV7: E24.SIG, TP16.2, U15.54
TX1_LV: R2.P4, U3.42
TX1_LV1: R22.P4, U1.42
TX1_LV2: R41.P4, U4.42
TX1_LV3: R58.P4, U7.42
TX1_LV4: R75.P4, U9.42
TX1_LV5: R92.P4, U11.42
TX1_LV6: R109.P4, U13.42
TX1_LV7: R126.P4, U15.42
TX2_LV: R4.P1, U3.27
TX2_LV1: R25.P1, U1.27
TX2_LV2: R44.P1, U4.27
TX2_LV3: R61.P1, U7.27
TX2_LV4: R78.P1, U9.27
TX2_LV5: R95.P1, U11.27
TX2_LV6: R112.P1, U13.27
TX2_LV7: R129.P1, U15.27
TXO1: J13.6, J15.2, R25.P8
TXO2: J1.2, J7.6, R4.P8
TXO3: J21.6, J23.2, R44.P8
TXO4: J29.6, J31.2, R61.P8
TXO5: J37.6, J39.2, R78.P8
TXO6: J45.6, J47.2, R95.P8
TXO7: J53.6, J55.2, R112.P8
TXO8: J61.6, J63.2, R129.P8
TXO/CIPO: J7.2, R2.P5
TXO/CIPO1: J13.2, R22.P5
TXO/CIPO2: J21.2, R41.P5
TXO/CIPO3: J29.2, R58.P5
TXO/CIPO4: J37.2, R75.P5
TXO/CIPO5: J45.2, R92.P5
TXO/CIPO6: J53.2, R109.P5
TXO/CIPO7: J61.2, R126.P5
TX_READY: J8.2, R3.P5
TX_READY1: J16.2, R23.P5
TX_READY2: J24.2, R42.P5
TX_READY3: J32.2, R59.P5
TX_READY4: J40.2, R76.P5
TX_READY5: J48.2, R93.P5
TX_READY6: J56.2, R110.P5
TX_READY7: J64.2, R127.P5
TX_READY_LV: R3.P4, U3.46
TX_READY_LV1: R23.P4, U1.46
TX_READY_LV2: R42.P4, U4.46
TX_READY_LV3: R59.P4, U7.46
TX_READY_LV4: R76.P4, U9.46
TX_READY_LV5: R93.P4, U11.46
TX_READY_LV6: R110.P4, U13.46
TX_READY_LV7: R127.P4, U15.46
UNP_D+: D6.3, J5.A6, J5.B6
UNP_D+1: D1.3, J9.A6, J9.B6
UNP_D+2: D15.3, J17.A6, J17.B6
UNP_D+3: D22.3, J25.A6, J25.B6
UNP_D+4: D29.3, J33.A6, J33.B6
UNP_D+5: D36.3, J41.A6, J41.B6
UNP_D+6: D43.3, J49.A6, J49.B6
UNP_D+7: D50.3, J57.A6, J57.B6
UNP_D-: D6.1, J5.A7, J5.B7
UNP_D-1: D1.1, J9.A7, J9.B7
UNP_D-2: D15.1, J17.A7, J17.B7
UNP_D-3: D22.1, J25.A7, J25.B7
UNP_D-4: D29.1, J33.A7, J33.B7
UNP_D-5: D36.1, J41.A7, J41.B7
UNP_D-6: D43.1, J49.A7, J49.B7
UNP_D-7: D50.1, J57.A7, J57.B7
V_BACKUP: B1.+, C10.1, R1.1, U3.36
V_BACKUP1: B2.+, C14.1, R32.1, U1.36
V_BACKUP2: B3.+, C21.1, R49.1, U4.36
V_BACKUP3: B4.+, C28.1, R66.1, U7.36
V_BACKUP4: B5.+, C35.1, R83.1, U9.36
V_BACKUP5: B6.+, C42.1, R100.1, U11.36
V_BACKUP6: B7.+, C49.1, R117.1, U13.36
V_BACKUP7: B8.+, C56.1, R134.1, U15.36

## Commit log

2021-10-25 Add ignore, license, and readme.
2021-10-25 Add missing PROD IDs
2021-10-27 Change RF trace width and other small changes from design review.
2021-10-29 Add production panel.
2022-01-11 Update README.md
    Updating README file for product release.
2023-04-24 Updating ZED-F9T-00B Datasheet
    Adding latest ZED-F9T-00B datasheet release (April, 2023).
2023-04-24 Delete ZED-F9T-00B_DataSheet_(UBX-18053713)
    Removing old ZED-F9T-00B datasheet that was replaced with latest release (April, 2023).
